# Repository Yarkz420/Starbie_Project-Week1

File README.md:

Hello, this is PCB design after completing week 1 of halflife.

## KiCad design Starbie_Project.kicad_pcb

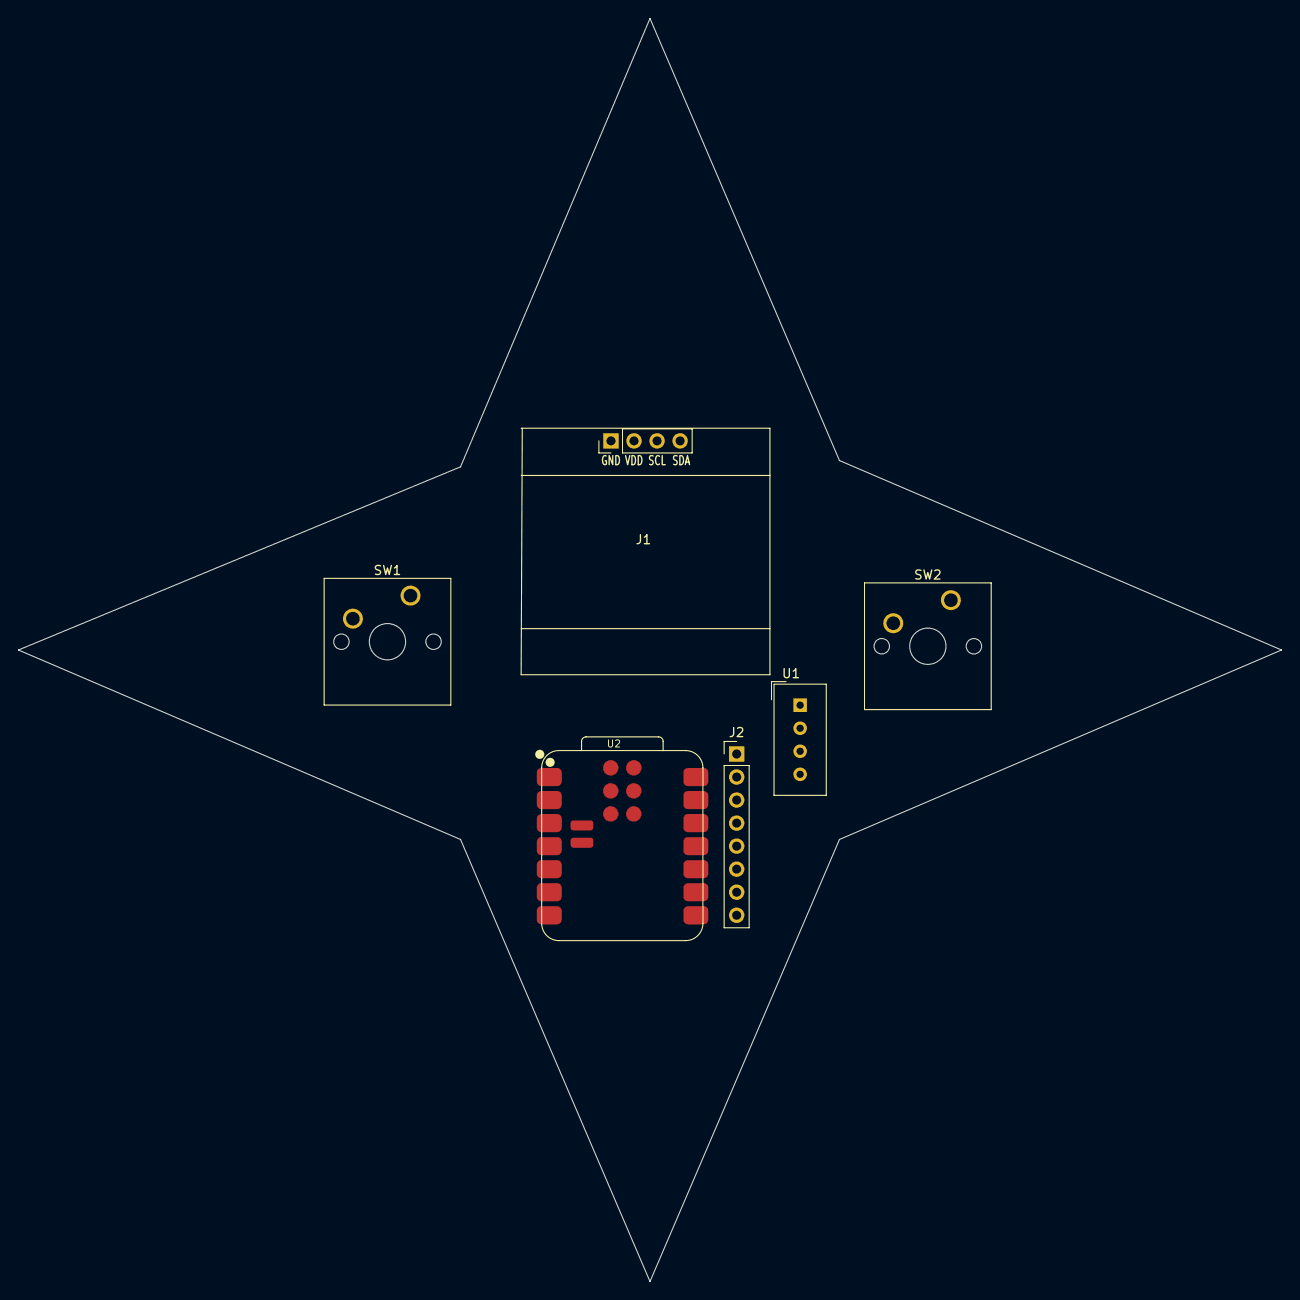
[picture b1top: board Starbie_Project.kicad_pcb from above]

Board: 2 copper layers, 139.3 x 139.3 mm, 6 parts (0 on the bottom side), 2 nets, no tracks yet.

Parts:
J1: Conn_01x04_Pin; Display_128x64_096_I2C
J2: Conn_01x08_Pin; PinHeader_1x08_P2.54mm_Vertical
SW1, SW2: SW_Push; SW_Cherry_MX_1.00u_PCB
U1: XIAO-ESP32-C3-SMD; Aosong_DHT11_5.5x12.0_P2.54mm
U2: DHT11; XIAO-ESP32-C3-SMD

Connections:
+3.3V: J1.3, J2.1, U2.1 (VDD)
GND: J1.4, J2.2, SW1.2 (2_2), SW2.2 (2_2), U2.4 (GND)
